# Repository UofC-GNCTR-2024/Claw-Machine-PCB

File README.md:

# Claw-Machine-PCB
PCB for the UofC GNCTR 2024 claw machine

## Main Components
1. 3x Stepper Motor Drivers
    * 2x will drive Y-axis, and 1x will drive X-axis
    * Model: A4988 Breakout
        * [Guide 1 - lastminuteengineers.com](https://lastminuteengineers.com/a4988-stepper-motor-driver-arduino-tutorial/)
    * The [microstep mode](https://lastminuteengineers.com/a4988-stepper-motor-driver-arduino-tutorial/#:~:text=power%20supply%20pins.-,Microstep%20Selection%20Pins,-The%20A4988%20driver) is locked in 1/16th Step Mode.
    * Add LEDs to each control signal
    * Signals (MCU to Driver, for each driver): STEP, DIR, EN

2. 1x DC Motor Driver
    * 1x for the claw to drop
    * Model: L298N (package: multiwatt vertical)
        * [Datasheet 1](https://www.sparkfun.com/datasheets/Robotics/L298_H_Bridge.pdf)
    * L298N contains 2x H-Bridges, so it can drive the 2x motors
    * Add LEDs to each control signal

3. Countdown Clock I2C Connector
    * Uses I2C (so only one bus)
    * Connection over 2.54mm headers

4. 10x Buttons and Limit Switches
    * 3x Limit Switches, 3x User Buttons, 2x Spare
    * Use 5.08mm screw terminal in parallel with 2.54mm header
    * Make them active-low, with external pull-up resistors
    * Put them in parallel with 6mm through-hole push buttons for validation

5. Control Stick
    * Model: [4-Way Switched Discrete Joystick](https://www.amazon.ca/Joystick-Classic-Competition-Arcade1up-Replacement/dp/B0BWWW8Z2J/ref=sr_1_15)
    * Basically 4x more buttons
    * Label them NESW, and use a common GND (5-pin 2.54mm header, but two of them side-by-side)

6. 1x Microcontroller System
    * Model: Arduino Mega 2560 clone
    * Footprint available via plugin

7. 4x General Power Output Channels
    * Use AO3420 MOSFETs, to be able to drive LEDs in the frame, etc.
    * Add a 3-way solder jumper to select between 5V or 12V power
    * Can be used fo LED strip lighting. One channel will be for the 12V claw solenoid.

8. Voltage Input Rails
    * 5V and 12V rails
    * Inputs via 5.08mm screw terminals
    * Powered from computer PSU

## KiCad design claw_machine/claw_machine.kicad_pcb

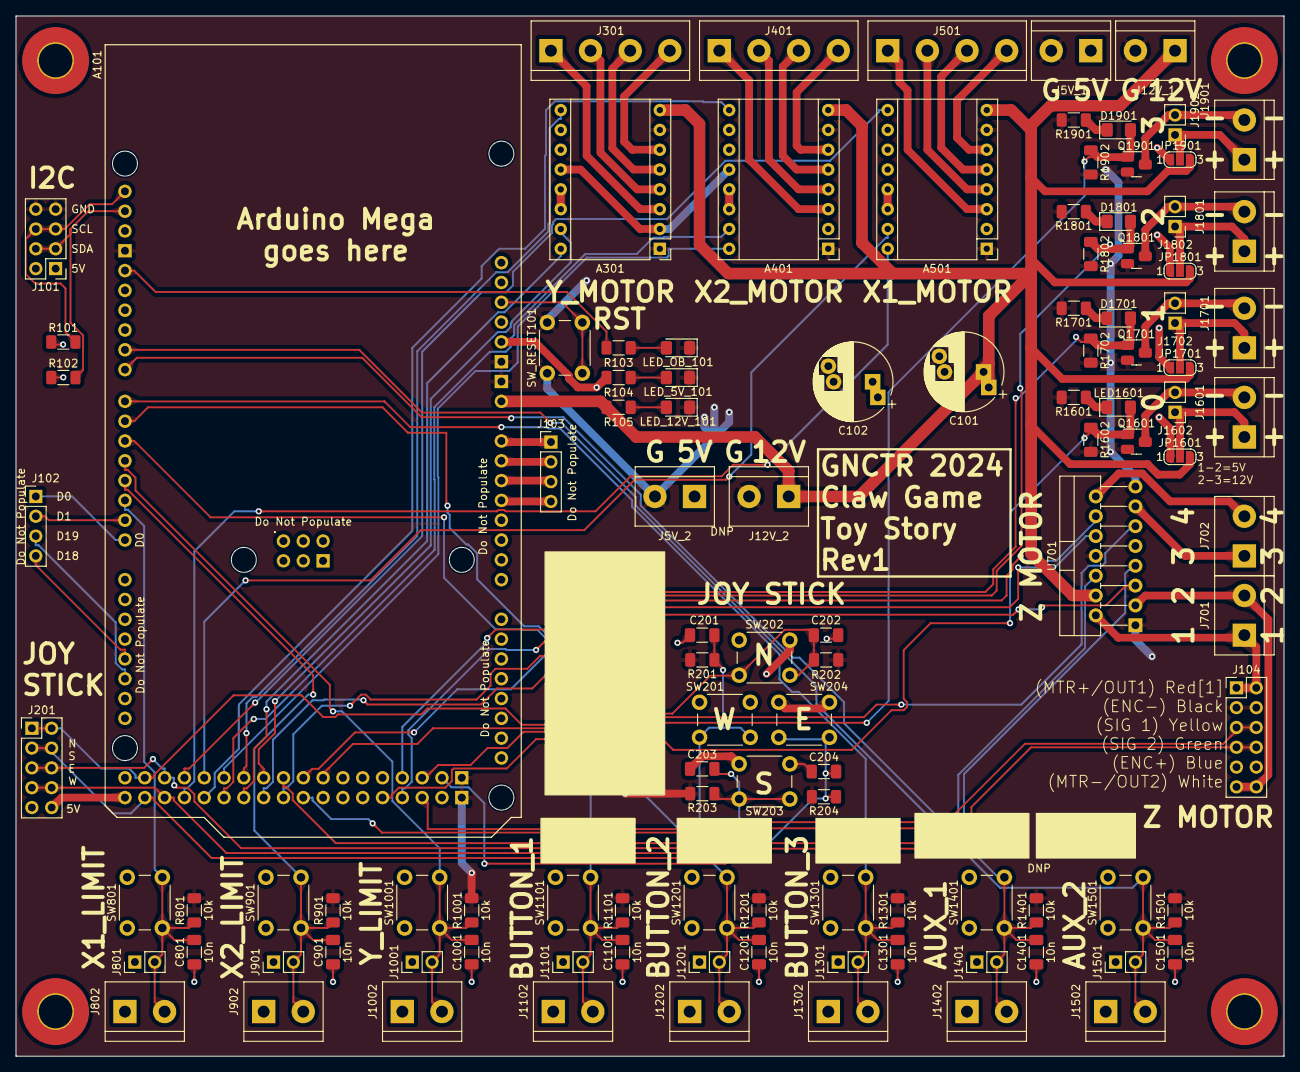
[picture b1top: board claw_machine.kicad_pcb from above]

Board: 2 copper layers, 162.6 x 133.4 mm, 114 parts (1 on the bottom side), 82 nets.

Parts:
A101: Arduino_Mega2560_R3_Shield
A301, A401, A501: Pololu_Breakout_A4988; Pololu_Breakout-16_15.2x20.3mm
C101, C102: 100u; CP_Radial_D10.0mm_P5.00mm_P7.50mm
C201, C202, C203, C204, C801, C901, C1001, C1101, C1201, C1301, C1401, C1501: 10n; C_1206_3216Metric_Pad1.33x1.80mm_HandSolder
D1701, D1801, D1901: LED; LED_1206_3216Metric_Pad1.42x1.75mm_HandSolder
H101, H102, H103, H104: MountingHole; MountingHole_4.3mm_M4_Pad_TopBottom
J5V_1, J5V_2, J12V_1, J12V_2, J701, J702, J802, J902, J1002, J1102, J1202, J1302, J1402, J1502, J1601, J1701, J1801, J1901: Screw_Terminal_01x02; TerminalBlock_bornier-2_P5.08mm
J101: PinHeader_2x04_P2.54mm_Vertical
J102, J103: Conn_01x04; PinHeader_1x04_P2.54mm_Vertical
J104: Conn_02x06_Odd_Even; PinHeader_2x06_P2.54mm_Vertical
J201: Conn_02x05_Odd_Even; PinHeader_2x05_P2.54mm_Vertical
J301, J401, J501: Screw_Terminal_01x04; TerminalBlock_bornier-4_P5.08mm
J801, J901, J1001, J1101, J1201, J1301, J1401, J1501, J1602, J1702, J1802, J1902: Conn_01x02; PinHeader_1x02_P2.54mm_Vertical
JP1601, JP1701, JP1801, JP1901: SolderJumper_3_Open; SolderJumper-3_P1.3mm_Open_RoundedPad1.0x1.5mm_NumberLabels
LED1601: LED; LED_1206_3216Metric_Pad1.42x1.75mm_HandSolder
LED_5V_101, LED_12V_101: LED; LED_1206_3216Metric_Pad1.42x1.75mm_HandSolder
LED_OB_101: LED; LED_1206_3216Metric_Pad1.42x1.75mm_HandSolder
Q1601, Q1701, Q1801, Q1901: AO3400A; SOT-23-MassivePads-HandSolder
R101, R102: 3k3; R_1206_3216Metric_Pad1.30x1.75mm_HandSolder
R103, R104, R1601, R1701, R1801, R1901: 2k2; R_1206_3216Metric_Pad1.30x1.75mm_HandSolder
R105, R201, R202, R203, R204, R801, R901, R1001, R1101, R1201, R1301, R1401, R1501, R1602, R1702, R1802, R1902: 10k; R_1206_3216Metric_Pad1.30x1.75mm_HandSolder
SW201, SW202, SW203, SW204, SW801, SW901, SW1001, SW1101, SW1201, SW1301, SW1401, SW1501: SW_Push; SW_PUSH_6mm
SW_RESET101: SW_Push; SW_PUSH_6mm
U701: L298N; TO-220-15_P2.54x2.54mm_StaggerOdd_Lead4.58mm_Vertical

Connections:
+5V: A101.5V1 (5V), A101.5V3 (5V), A101.5V4 (5V), A301.2 (VDD), A301.10 (MS1), A301.11 (MS2), A301.12 (MS3), A401.2 (VDD), A401.10 (MS1), A401.11 (MS2), A401.12 (MS3), A501.2 (VDD), A501.10 (MS1), A501.11 (MS2), A501.12 (MS3), C102.1, C201.1, C202.1, C203.1, C204.1, C801.1, C901.1, C1001.1, C1101.1, C1201.1, C1301.1, C1401.1, C1501.1, J5V_1.1, J5V_2.1, J101.1, J101.2, J104.9, J104.10, J201.9, J201.10, J801.1, J802.1, J901.1, J902.1, J1001.1, J1002.1, J1101.1, J1102.1, J1201.1, J1202.1, J1301.1, J1302.1, J1401.1, J1402.1, J1501.1, J1502.1, JP1601.1 (A), JP1701.1 (A), JP1801.1 (A), JP1901.1 (A), R101.1, R102.1, R104.1, SW201.1, SW202.1, SW203.1, SW204.1, SW801.1, SW901.1, SW1001.1, SW1101.1, SW1201.1, SW1301.1, SW1401.1, SW1501.1, U701.9 (Vss)
+12V: A101.VIN, A301.8 (VMOT), A401.8 (VMOT), A501.8 (VMOT), C101.1, J12V_1.1, J12V_2.1, JP1601.3 (B), JP1701.3 (B), JP1801.3 (B), JP1901.3 (B), R105.1, U701.4 (Vs)
/AUX_SW_1: A101.D8, C1401.2, J1401.2, J1402.2, R1401.1, SW1401.2
/AUX_SW_2: A101.D9, C1501.2, J1501.2, J1502.2, R1501.1, SW1501.2
/GENERAL_PWR_EN_0: A101.D47, LED1601.2 (A), Q1601.1 (G), R1602.1
/GENERAL_PWR_EN_1: A101.D48, D1701.2 (A), Q1701.1 (G), R1702.1
/GENERAL_PWR_EN_2: A101.D49, D1801.2 (A), Q1801.1 (G), R1802.1
/GENERAL_PWR_EN_3: A101.D50 (D50_MISO), D1901.2 (A), Q1901.1 (G), R1902.1
/INPUT_BTN_1: A101.D5, C1101.2, J1101.2, J1102.2, R1101.1, SW1101.2
/INPUT_BTN_2: A101.D6, C1201.2, J1201.2, J1202.2, R1201.1, SW1201.2
/INPUT_BTN_3: A101.D7, C1301.2, J1301.2, J1302.2, R1301.1, SW1301.2
/ONBOARD_LED: A101.D13, R103.1
/X1_DIR: A101.D28, A501.15 (STEP)
/X1_LIMIT: A101.D2 (D2_INT0), C801.2, J801.2, J802.2, R801.1, SW801.2
/X1_STEP: A101.D27, A501.16 (DIR)
/X2_DIR: A101.D31, A401.15 (STEP)
/X2_LIMIT: A101.D3 (D3_INT1), C901.2, J901.2, J902.2, R901.1, SW901.2
/X2_STEP: A101.D30, A401.16 (DIR)
/Y_DIR: A101.D34, A301.15 (STEP)
/Y_LIMIT: A101.D4, C1001.2, J1001.2, J1002.2, R1001.1, SW1001.2
/Y_STEP: A101.D33, A301.16 (DIR)
/Z_DC_EN_A: A101.D39, U701.6 (EnA)
/Z_DC_EN_B: A101.D40, U701.11 (EnB)
/Z_DC_IN1: A101.D35, U701.5 (IN1)
/Z_DC_IN2: A101.D36, U701.7 (IN2)
/Z_DC_IN3: A101.D37, U701.10 (IN3)
/Z_DC_IN4: A101.D38, U701.12 (IN4)
/Z_ENC_SIG_1: A101.D51 (D51_MOSI), J104.5, J104.6
/Z_ENC_SIG_2: A101.D52 (D52_SCK), J104.7, J104.8
/Z_OUT1: J104.1, J104.2, J701.1, U701.2 (OUT1)
/Z_OUT2: J104.11, J104.12, J701.2, U701.3 (OUT2)
/control_stick/EAST_BTN: A101.D23, C204.2, J201.3, J201.4, R204.1, SW204.2
/control_stick/NORTH_BTN: A101.D22, C202.2, J201.1, J201.2, R202.1, SW202.2
/control_stick/SOUTH_BTN: A101.D24, C203.2, J201.5, J201.6, R203.1, SW203.2
/control_stick/WEST_BTN: A101.D25, C201.2, J201.7, J201.8, R201.1, SW201.2
/dc_driver_z/ OUT3: J702.1, U701.13 (OUT3)
/dc_driver_z/ OUT4: J702.2, U701.14 (OUT4)
/~X1_EN: A101.D26, A501.9 (~ENABLE)
/~X2_EN: A101.D29, A401.9 (~ENABLE)
/~Y_EN: A101.D32, A301.9 (~ENABLE)
GND: A101.GND1 (GND), A101.GND2 (GND), A101.GND3 (GND), A101.GND5 (GND), A101.GND6 (GND), A301.1 (GND), A301.7 (GND), A401.1 (GND), A401.7 (GND), A501.1 (GND), A501.7 (GND), C101.2, C102.2, J5V_1.2, J5V_2.2, J12V_1.2, J12V_2.2, J101.7, J101.8, J104.3, J104.4, LED_5V_101.1 (K), LED_12V_101.1 (K), LED_OB_101.1 (K), Q1601.2 (S), Q1701.2 (S), Q1801.2 (S), Q1901.2 (S), R201.2, R202.2, R203.2, R204.2, R801.2, R901.2, R1001.2, R1101.2, R1201.2, R1301.2, R1401.2, R1501.2, R1601.2, R1602.2, R1701.2, R1702.2, R1801.2, R1802.2, R1901.2, R1902.2, SW_RESET101.1, U701.1 (SENSE_A), U701.8 (GND), U701.15 (SENSE_B)
I2C_SCL: A101.SCL, J101.5, J101.6, R101.2
I2C_SDA: A101.SDA, J101.3, J101.4, R102.2
unnamed: A101.D0 (D0/RX0), J102.1
unnamed: A101.D1 (D1/TX0), J102.2
unnamed: A101.D18 (D18/TX1), J102.4
unnamed: A101.D19 (D19/RX1), J102.3
unnamed: A101.RST1 (RESET), SW_RESET101.2
unnamed: A301.4 (1A), J301.2
unnamed: A301.3 (1B), J301.1
unnamed: A301.5 (2A), J301.3
unnamed: A301.6 (2B), J301.4
unnamed: A301.13 (~RESET), A301.14 (~SLEEP)
unnamed: A401.4 (1A), J401.2
unnamed: A401.3 (1B), J401.1
unnamed: A401.5 (2A), J401.3
unnamed: A401.6 (2B), J401.4
unnamed: A401.13 (~RESET), A401.14 (~SLEEP)
unnamed: A501.4 (1A), J501.2
unnamed: A501.3 (1B), J501.1
unnamed: A501.5 (2A), J501.3
unnamed: A501.6 (2B), J501.4
unnamed: A501.13 (~RESET), A501.14 (~SLEEP)
unnamed: D1701.1 (K), R1701.1
unnamed: D1801.1 (K), R1801.1
unnamed: D1901.1 (K), R1901.1
unnamed: A101.A0, J103.1
unnamed: A101.A1, J103.2
unnamed: A101.A2, J103.3
unnamed: A101.A3, J103.4
unnamed: J1601.1, J1602.1, JP1601.2 (C)
unnamed: J1601.2, J1602.2, Q1601.3 (D)
unnamed: J1701.1, J1702.1, JP1701.2 (C)
unnamed: J1701.2, J1702.2, Q1701.3 (D)
unnamed: J1801.1, J1802.1, JP1801.2 (C)
unnamed: J1801.2, J1802.2, Q1801.3 (D)
unnamed: J1901.1, J1902.1, JP1901.2 (C)
unnamed: J1901.2, J1902.2, Q1901.3 (D)
unnamed: LED1601.1 (K), R1601.1
unnamed: LED_5V_101.2 (A), R104.2
unnamed: LED_12V_101.2 (A), R105.2
unnamed: LED_OB_101.2 (A), R103.2

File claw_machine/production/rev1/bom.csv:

Designator,Footprint,Quantity,Value,LCSC Part #
A101,Arduino_Mega2560_R3_Shield,1,Arduino_Mega2560_R3_Shield,
"A301, A401, A501",Pololu_Breakout-16_15.2x20.3mm,3,Pololu_Breakout_A4988,
"C1001, C1101, C1201, C1301, C1401, C1501, C201, C202, C203, C204, C801, C901",1206,12,10n,
"C101, C102",CP_Radial_D10.0mm_P5.00mm_P7.50mm,2,100u,
"D1701, D1801, D1901, LED1601, LED_12V_101, LED_5V_101, LED_OB_101",1206,7,LED,
"H101, H102, H103, H104",MountingHole_4.3mm_M4_Pad_TopBottom,4,MountingHole,
"J1001, J1101, J1201, J1301, J1401, J1501, J1602, J1702, J1802, J1902, J801, J901",PinHeader_1x02_P2.54mm_Vertical,12,Conn_01x02,
"J1002, J1102, J1202, J12V_1, J1302, J1402, J1502, J1601, J1701, J1801, J1901, J5V_1, J701, J702, J802, J902",TerminalBlock_bornier-2_P5.08mm,16,Screw_Terminal_01x02,
J101,PinHeader_2x04_P2.54mm_Vertical,1,~,
"J102, J103",PinHeader_1x04_P2.54mm_Vertical,2,Conn_01x04,
J104,PinHeader_2x06_P2.54mm_Vertical,1,Conn_02x06_Odd_Even,
J201,PinHeader_2x05_P2.54mm_Vertical,1,Conn_02x05_Odd_Even,
"J301, J401, J501",TerminalBlock_bornier-4_P5.08mm,3,Screw_Terminal_01x04,
"JP1601, JP1701, JP1801, JP1901",SolderJumper-3_P1.3mm_Open_RoundedPad1.0x1.5mm_NumberLabels,4,SolderJumper_3_Open,
"Q1601, Q1701, Q1801, Q1901",SOT-23-MassivePads-HandSolder,4,AO3400A,
"R1001, R105, R1101, R1201, R1301, R1401, R1501, R1602, R1702, R1802, R1902, R201, R202, R203, R204, R801, R901",1206,17,10k,
"R101, R102",1206,2,3k3,
"R103, R104, R1601, R1701, R1801, R1901",1206,6,2k2,
"SW1001, SW1101, SW1201, SW1301, SW1401, SW1501, SW201, SW202, SW203, SW204, SW801, SW901, SW_RESET101",SW_PUSH_6mm,13,SW_Push,
U701,TO-220-15_P2.54x2.54mm_StaggerOdd_Lead4.58mm_Vertical,1,L298N,

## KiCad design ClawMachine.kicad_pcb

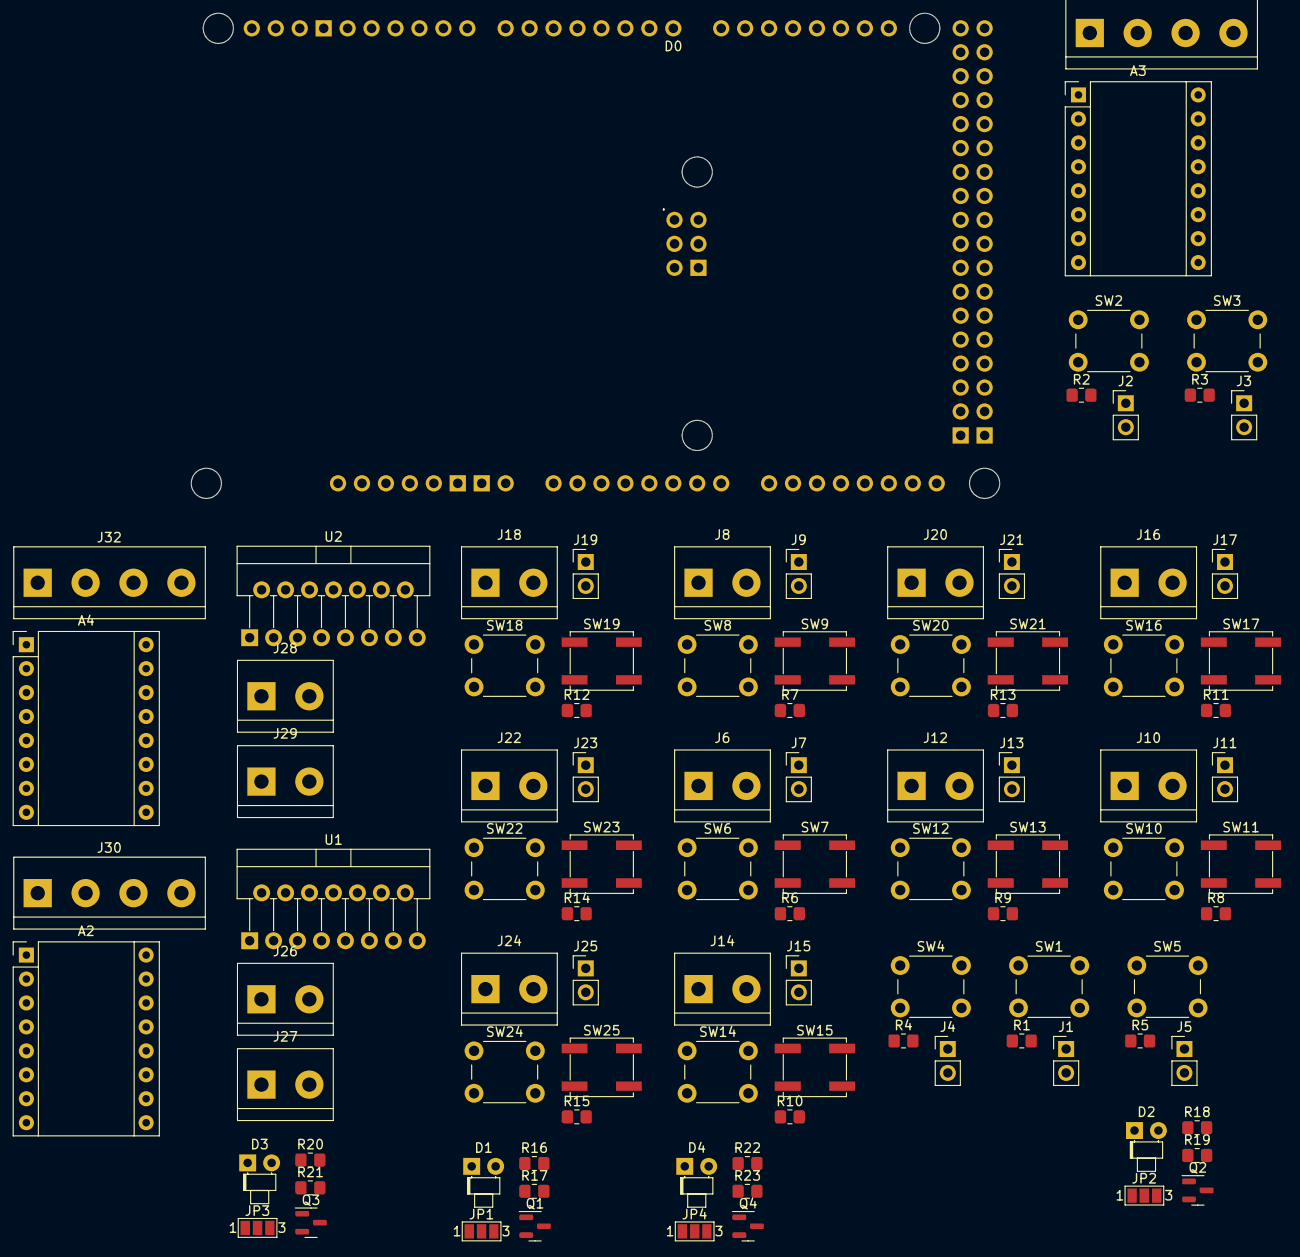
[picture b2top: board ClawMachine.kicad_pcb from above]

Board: 2 copper layers, 98 parts (0 on the bottom side), 11 nets, no tracks yet.

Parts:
A1: Arduino_Mega2560_R3_Shield
A2, A3, A4: Pololu_Breakout_A4988; Pololu_Breakout-16_15.2x20.3mm
D1, D2, D3, D4: LED; LED_D1.8mm_W1.8mm_H2.4mm_Horizontal_O1.27mm_Z1.6mm
J1, J2, J3, J4, J5, J7, J9, J11, J13, J15, J17, J19, J21, J23, J25: Conn_01x02_Pin; PinHeader_1x02_P2.54mm_Vertical
J6, J8, J10, J12, J14, J16, J18, J20, J22, J24, J26, J27, J28, J29: Screw_Terminal_01x02; TerminalBlock_bornier-2_P5.08mm
J30, J31, J32: Screw_Terminal_01x04; TerminalBlock_bornier-4_P5.08mm
JP1, JP2, JP3, JP4: SolderJumper_3_Open; SolderJumper-3_P1.3mm_Open_Pad1.0x1.5mm_NumberLabels
Q1, Q2, Q3, Q4: AO3400A; SOT-23
R1, R2, R3, R4, R5, R6, R7, R8, R9, R10, R11, R12, R13, R14, R15: R_US; R_0805_2012Metric_Pad1.20x1.40mm_HandSolder
R16, R17, R18, R19, R20, R21, R22, R23: R; R_0805_2012Metric_Pad1.20x1.40mm_HandSolder
SW1, SW2, SW3, SW4, SW5, SW6, SW8, SW10, SW12, SW14, SW16, SW18, SW20, SW22, SW24: SW_Push; SW_PUSH_6mm
SW7, SW9, SW11, SW13, SW15, SW17, SW19, SW21, SW23, SW25: SW_SPST; SW_SPST_EVQP0
U1, U2: L298N; TO-220-15_P2.54x2.54mm_StaggerOdd_Lead4.58mm_Vertical

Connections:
unnamed: A3.4 (1A), J31.2
unnamed: A3.3 (1B), J31.1
unnamed: A3.5 (2A), J31.3
unnamed: A3.6 (2B), J31.4
unnamed: A3.13 (~RESET), A3.14 (~SLEEP)
unnamed: J28.2, U2.3 (OUT2)
unnamed: J29.2, U2.14 (OUT4)
unnamed: Q1.1 (G), R16.2, R17.1
unnamed: Q2.1 (G), R18.2, R19.1
unnamed: Q3.1 (G), R20.2, R21.1
unnamed: Q4.1 (G), R22.2, R23.1

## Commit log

2023-10-11 Add design plan
2023-10-21 Init
2023-10-21 make more modular
2023-10-23 add clk, drivers & pwr
2023-10-23 add pcb? i think
2023-10-23 Fix .gitignore files
2023-10-23 change folder stuff & update gen pwr
2023-10-23 update limit switches to active high
2023-10-27 Rework schematic
2023-10-27 Remove deleted sheets
2023-10-27 Assign footprints
2023-10-27 Tiny bit of PCB work
2023-10-27 Start PCB work
2023-10-27 Do most of the PCB layout
2023-10-27 Route all power traced and replicated sections
2023-10-27 Minor change reconcile
2023-10-28 Autoroute and clean up manually
2023-10-28 Tweaks
2023-10-28 Add teardrops
2023-10-28 Add names
2023-10-28 Finish, Gerbers
2023-11-03 Lock in rev1 production products, docs
2023-11-09 Rename rev1 production files
2023-11-12 Update schematic text, remove unused nets for CLAW motor
2023-12-10 Save STEP export location
